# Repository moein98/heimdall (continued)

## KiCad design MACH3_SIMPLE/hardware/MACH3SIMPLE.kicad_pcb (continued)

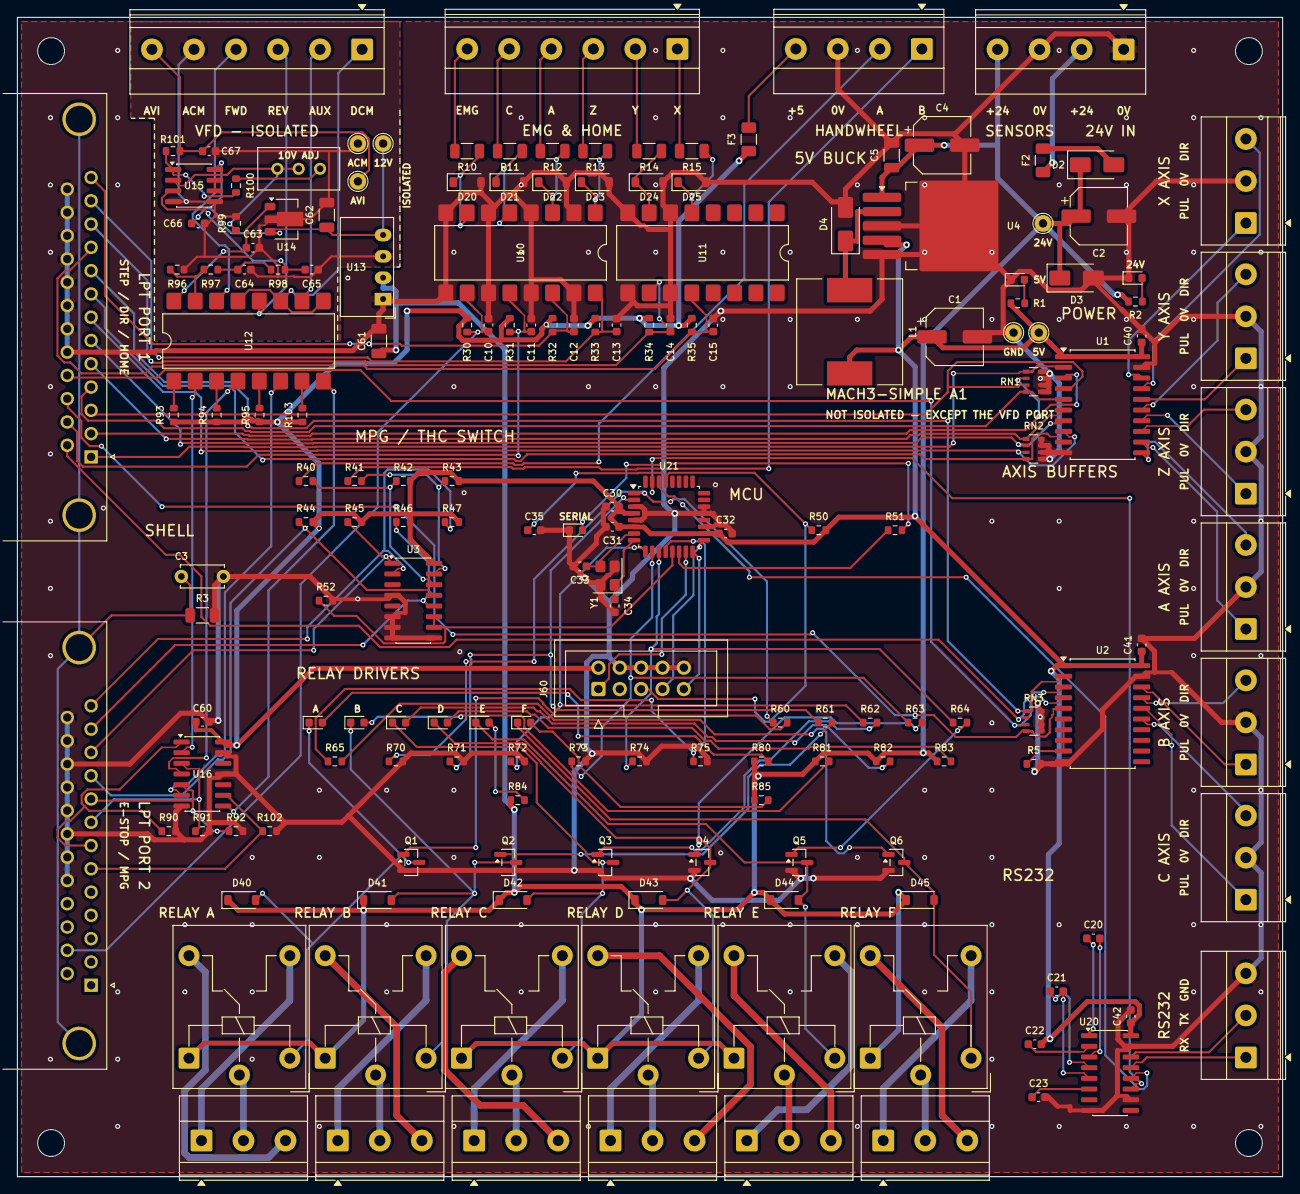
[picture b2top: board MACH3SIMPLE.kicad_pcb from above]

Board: 2 copper layers, 150.5 x 137.9 mm, 178 parts (0 on the bottom side), 149 nets.

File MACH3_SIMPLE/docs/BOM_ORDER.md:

# MACH3-SIMPLE - order list

Generated from the netlist by `tools/bom.py`. Quantities are what the
board needs; buy spares of the 0603 passives and the optocouplers.

## Semiconductors - the ones to get right

| Qty | Part | Package | Refs | Note |
|---:|---|---|---|---|
| 2 | 74HC245 | SOIC-20W_7.5x12.8mm_P1.27mm | U1, U2 |  |
| 2 | PC847 | SOIC-16 | U10, U11 | 4-channel opto, DIP-16 outline in SOIC. PC844 is the same part |
| 1 | 74HC4053 | SOIC-16 | U3 |  |
| 1 | ATmega328P-AU | TQFP-32 | U21 | TQFP-32. Runs on the 16 MHz crystal Y1 |
| 1 | MAX3232 | SOIC-16 | U20 | 3 V version works on 5 V; MAX232 does NOT - wrong capacitor values |

## Transistors, diodes and LEDs

| Qty | Part | Package | Refs | Note |
|---:|---|---|---|---|
| 9 | LED, indicator | 0603 SMD | D10, D11, D30, D50, D51, D52, D53, D54, D55 |  |
| 6 | 1N4148 | SOD-123 SMD | D40, D41, D42, D43, D44, D45 | plain small-signal, any maker |
| 6 | 2N7002 | SOT-23 | Q1, Q2, Q3, Q4, Q5, Q6 |  |
| 2 | SS34 | SMA SMD | D1, D2 | 40 V 3 A Schottky, both places |
| 1 | SMAJ26A | SMA SMD | D3 | TVS on the 24 V input. Clamps at 42 V, under the 50 V rating of C2 |

## Relays

| Qty | Part | Package | Refs | Note |
|---:|---|---|---|---|
| 6 | JQC-3FF-024-1Z | JQC-3FF relay, THT | K1, K2, K3, K4, K5, K6 | 24 V coil, SPDT. Songle or Hongfa |

## Connectors

| Qty | Part | Package | Refs | Note |
|---:|---|---|---|---|
| 13 | connector | Phoenix MKDS 1,5 5.0 mm, 3 way | J10, J11, J12, J13, J14, J15 ... J50 |  |
| 2 | connector | Phoenix MKDS 1,5 5.0 mm, 2 way | J3, J4 |  |
| 2 | connector | DB25 socket, right angle, PCB | J1, J2 |  |
| 1 | connector | Phoenix MKDS 1,5 5.0 mm, 6 way | J20 |  |
| 1 | connector | Phoenix MKDS 1,5 5.0 mm, 4 way | J30 |  |
| 1 | connector | 2x5 shrouded box header, 2.54 mm | J60 |  |

## Resistors

| Qty | Part | Package | Refs | Note |
|---:|---|---|---|---|
| 18 | 10k | 0603 SMD | R2, R30, R31, R32, R33, R34 ... R75 |  |
| 8 | 1k | 0603 SMD | R1, R51, R60, R61, R62, R63, R64, R65 |  |
| 8 | 4k7 | 0603 SMD | R42, R43, R80, R81, R82, R83, R84, R85 |  |
| 6 | 4k7 | 1206 SMD | R10, R11, R12, R13, R14, R15 |  |
| 3 | 4x10k | 4 x 0603 array, convex (1206 size) | RN1, RN2, RN3 |  |
| 2 | 330R | 0603 SMD | R40, R41 |  |
| 1 | 10k MPG_SEL | 0603 SMD | R52 |  |
| 1 | 10k spare | 0603 SMD | R5 |  |

## Capacitors

| Qty | Part | Package | Refs | Note |
|---:|---|---|---|---|
| 10 | 100nF | 0603 SMD | C20, C21, C22, C23, C30, C31, C32, C40, C41, C42 |  |
| 6 | 10nF | 0603 SMD | C10, C11, C12, C13, C14, C15 |  |
| 2 | 22pF | 0603 SMD | C33, C34 |  |
| 1 | 100uF 16V | electrolytic 6.3x7.7 SMD | C1 |  |
| 1 | 100uF 50V | electrolytic 6.3x7.7 SMD | C2 |  |
| 1 | 1nF 2kV | disc ceramic, THT | C3 |  |

## Inductor, fuse, crystal

| Qty | Part | Package | Refs | Note |
|---:|---|---|---|---|
| 2 | 1A slow | 1206 SMD | F1, F2 |  |
| 1 | 16MHz | 3.2x2.5 mm SMD, 4 pad | Y1 | load capacitance CL 18-20 pF, to suit the 22 pF capacitors |

## Mechanical

| Qty | Part | Package | Refs | Note |
|---:|---|---|---|---|
| 4 | M3 | M3 hole (no part) | H1, H2, H3, H4 |  |

## Not fitted - leave the pads empty

- R3 (0R link - DO NOT FIT)

**128 parts to fit** across 33 distinct lines.

Worth buying spare: the 0603 resistors and capacitors (they are pennies and
they get lost), one or two extra PC847, and one spare ATmega328P.

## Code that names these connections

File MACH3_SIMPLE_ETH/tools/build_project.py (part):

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# ---------------------------------------------------------------------------
# The RP2350B pin map. Keep in step with docs/SPEC.md and my_machine_map.h;
# tools/check_pinmap.py compares all three.
GPIO = {0: 'RS485_DI', 1: 'RS485_RO'}
for _i, _a in enumerate(AXES):
    GPIO[2 + _i] = '%s_STEP3' % _a           # PIO, consecutive
    GPIO[10 + _i] = '%s_DIR3' % _a           # consecutive
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                  footprint='Diode_SMD:D_SMA', rot=270)
    c24 = s.place('Device', 'C_Polarized', 'C104', '47uF 50V', 345.44, 88.9,
                  footprint='Capacitor_SMD:CP_Elec_6.3x7.7')
    s.net(j24, TOP_PIN(2, 4), 'VIN24')
    s.net(f24, 1, 'VIN24')
    s.link(f24, 2, d24, 2, 'VIN24F')
    s.link(d24, 1, tvs, 1, 'V24', via_y=76.2)
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    s.net(mcu, pins['ADC_AVDD'][0], '+3V3')
    s.net(mcu, pins['VREG_VIN'][0], '+3V3')
    s.net(mcu, pins['VREG_PGND'][0], 'GND')
    s.net(mcu, pins['VREG_LX'][0], 'VREG_LX')
    s.net(mcu, pins['VREG_FB'][0], '+1V1')
    s.net(mcu, pins['VREG_AVDD'][0], 'VREG_AVDD')
    s.net(mcu, pins['XIN'][0], 'XIN')
    s.net(mcu, pins['XOUT'][0], 'XOUT')
    s.net(mcu, pins['RUN'][0], 'NRST')
    s.net(mcu, pins['SWCLK'][0], 'SWCLK')
    s.net(mcu, pins['SWDIO'][0], 'SWDIO')
    s.net(mcu, pins['USB_DP'][0], 'USB_DP_MCU')
    s.net(mcu, pins['USB_DM'][0], 'USB_DM_MCU')
    for nm in ('QSPI_SD0', 'QSPI_SD1', 'QSPI_SD2', 'QSPI_SD3', 'QSPI_SCLK'):
        s.net(mcu, pins[nm][0], nm)
    s.net(mcu, pins['~{QSPI_SS}'][0], 'QSPI_SS')
    s.nc_rest(mcu)

    s.box(12.7, 35.56, 127.0, 157.48, 'CORE SUPPLY - INTERNAL SWITCHER')
    s.text('VREG_LX -> L201 -> +1V1 (DVDD). Tight loop to pins 62-65.', 15.24, 43.18)
    l = s.place('Device', 'L', 'L201', '3.3uH 2016 shielded', 50.8, 63.5,
                footprint='Inductor_SMD:L_Murata_DFE201610P', rot=90)
    s.net(l, 1, 'VREG_LX')
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
    rj = s.place('Connector', 'RJ45_Hanrun_HR911105A_Horizontal', 'J301', 'HR911105A',
                 495.3, 119.38, footprint='Connector_RJ:RJ45_Hanrun_HR911105A_Horizontal')
    for pin, net in (('1', 'ETH_TDP'), ('2', 'ETH_TDN'), ('4', 'ETH_TCT'),
                     ('3', 'ETH_RDP'), ('6', 'ETH_RDN'), ('5', 'ETH_RCT'),
                     ('8', 'CHASSIS'), ('SH', 'CHASSIS')):
        s.net(rj, pin, net)
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    s.net(tv, 3, 'GND')
    t = s.place('Connector', 'Conn_01x03_Pin', 'J801', 'RS485 A B GND', 223.52, 101.6,
                footprint=TERM % (3, 3))
    s.net(t, TOP_PIN(0, 3), 'RS485_A')
    s.net(t, TOP_PIN(1, 3), 'RS485_B')
    s.net(t, TOP_PIN(2, 3), 'GND')

    s.box(12.7, 165.1, 482.6, 381.0, 'HANDWHEEL MCU - ATmega328P, 3.3 V, 8 MHz, UART1 TO THE RP2350')
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    s.net(m, by['GND'], 'GND')
    s.net(m, by['AVCC'], '+3V3')
    s.nc(m, by['AREF'])
    s.net(m, by['~{RESET}/PC6'], 'HW_RESET')
    s.net(m, by['XTAL1/PB6'], 'HW_XTAL1')
    s.net(m, by['XTAL2/PB7'], 'HW_XTAL2')
    # RP2350 UART1 TX (GP42) -> ATmega RXD; ATmega TXD -> GP43.
    s.net(m, by['PD0'], 'UART1_TX')
    s.net(m, by['PD1'], 'UART1_RX')
    HW_PINS = (('PD2', 'MPG_A'), ('PD3', 'MPG_B'),          # INT0 / INT1
               ('PC0', 'MPG_SEL_X'), ('PC1', 'MPG_SEL_Y'), ('PC2', 'MPG_SEL_Z'),
               ('PC3', 'MPG_SEL_A'), ('PC4', 'MPG_SEL_B'), ('PC5', 'MPG_SEL_C'),
               ('PD4', 'MPG_SEL_U'), ('PD5', 'MPG_SEL_V'),
               ('PD6', 'MPG_X1'), ('PD7', 'MPG_X10'), ('PB0', 'MPG_X100'),
               ('PB1', 'HW_LED'),
               ('PB3', 'HW_MOSI'), ('PB4', 'HW_MISO'), ('PB5', 'HW_SCK'))
    for nm, net in HW_PINS:
        s.net(m, by[nm], net)
    s.nc_rest(m)
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    cap(s, 'C807', '22pF', 205.74, 368.3, 'HW_XTAL2', 'GND')
    isp = s.place('Connector', 'AVR-ISP-6', 'J802', 'HW ICSP', 205.74, 195.58,
                  footprint='Connector_PinHeader_2.54mm:PinHeader_2x03_P2.54mm_Vertical')
    for pin, net in (('1', 'HW_MISO'), ('2', '+3V3'), ('3', 'HW_SCK'), ('4', 'HW_MOSI'),
                     ('5', 'HW_RESET'), ('6', 'GND')):
        s.net(isp, pin, net)
    res(s, 'R805', '1k', 256.54, 220.98, 'HW_LED', 'HW_LED_A')
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
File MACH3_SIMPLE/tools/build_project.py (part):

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# nearest the top of the lower D-sub, the end closest to the spindle block.
# In Mach3: pin 7 is the spindle step/PWM pin, pin 8 Output #1 (M3, CW) and
# pin 9 Output #2 (M4, CCW).
P2_SPINDLE = [('7', 'SP_PWM_IN'), ('8', 'SP_FWD_IN'), ('9', 'SP_REV_IN'),
              ('6', 'SP_AUX_IN')]

# 24 V sensor channels, in the order they sit along the top edge.
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                  footprint='Capacitor_SMD:CP_Elec_6.3x7.7')
    # Labels, not a wire: pin 2 is drawn beside pin 1, and a wire from it to
    # the fuse would run across pin 1.
    s.net(j24, TOP_PIN(2, 4), 'VIN24')             # +24 in, third screw
    s.net(f24, 1, 'VIN24')
    s.link(f24, 2, d24, 2, 'VIN24F')
    s.link(d24, 1, tvs, 1, 'V24', via_y=76.2)
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    # The handwheel's +5V goes out on a cable, through a resettable fuse, so
    # a short in that cable trips F3 instead of pulling down the board's 5 V
    # rail and resetting the MCU with it.
    s.net(jm, TOP_PIN(0, 4), 'MPG_5V')
    pf = s.place('Device', 'Polyfuse', 'F3', '200mA hold PTC 1206', 190.5, 238.76,
                 footprint='Fuse:Fuse_1206_3216Metric')
    s.net(pf, 1, '+5V')
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    s.net(sw, '10', 'MPG_SEL')
    s.net(sw, '9', 'GND')            # C unused, its switch parked
    s.net(sw, '14', 'MPG_A_PC')      # X common: the conditioned A signal
    s.net(sw, '12', 'MPG_A_JOG')     # X0 -> port 2 pin 12
    s.net(sw, '13', 'MPG_A_THC')     # X1 -> port 2 pin 10
    s.net(sw, '15', 'MPG_B_PC')      # Y common
    s.net(sw, '2', 'MPG_B_JOG')      # Y0 -> port 2 pin 13
    s.net(sw, '1', 'MPG_B_THC')      # Y1 -> port 2 pin 11
    s.net(sw, '4', 'GND')            # Z switch unused
    s.nc(sw, '3')
    s.nc(sw, '5')
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    s.net(m, '8', 'GND')
    s.nc(m, '9')
    s.nc(m, '7')
    for pin, net in (('1', 'C1P'), ('3', 'C1N'), ('4', 'C2P'), ('5', 'C2N'),
                     ('2', 'VSP'), ('6', 'VSN')):
        s.net(m, pin, net)
    s.nc_rest(m)
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    c = s.place('Device', 'C', 'C42', '100nF', 63.5, 241.3, footprint=C0603)
    s.net(c, 1, '+5V')
    s.net(c, 2, 'GND')
    s.net(mcu, by['~{RESET}/PC6'] if '~{RESET}/PC6' in by else by.get('PC6', '29'),
          'MCU_RESET')
    rr = s.place('Device', 'R', 'R50', '10k', 25.4, 165.1, footprint=R0603)
    s.net(rr, 1, 'MCU_RESET')
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    cr = s.place('Device', 'C', 'C35', '10nF', 25.4, 190.5, footprint=C0603)
    s.net(cr, 1, 'MCU_RESET')
    s.net(cr, 2, 'GND')
    s.net(mcu, by['PD0'], 'MCU_RX')
    s.net(mcu, by['PD1'], 'MCU_TX')

    # A 16 MHz crystal. It was left off at first, by request, and put back
    # before the first order: the internal RC is trimmed only to within 10
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    xt = s.place('Device', 'Crystal_GND24', 'Y1', '16MHz',
                 101.6, 254.0,
                 footprint='Crystal:Crystal_SMD_3225-4Pin_3.2x2.5mm')
    s.net(mcu, by['XTAL1/PB6'], 'XTAL1')
    s.net(mcu, by['XTAL2/PB7'], 'XTAL2')
    s.net(xt, '3', 'XTAL1')
    s.net(xt, '1', 'XTAL2')
    s.net(xt, '2', 'GND')
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    # read back out of the netlist by firmware/test, which fails if the two
    # disagree.
    MCU_PINS = (
        ('PD3', 'REL_A'), ('PD4', 'REL_B'), ('PD5', 'REL_C'),
        ('PD6', 'REL_D'), ('PD7', 'REL_E'), ('PB0', 'REL_F'),
        ('PB1', 'MPG_SEL'),                   # SendSerial 'T' / 't'
        ('PB2', 'MCU_LED'),
        ('PB3', 'ICSP_MOSI'), ('PB4', 'ICSP_MISO'), ('PB5', 'ICSP_SCK'),
    )
    for nm, net in MCU_PINS:
        s.net(mcu, by[nm], net)
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
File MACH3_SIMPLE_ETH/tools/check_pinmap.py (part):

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difference.

It then follows each signal to where it must arrive (ETH_CS to the W5500's
SCS pin, UART1_TX to the handwheel MCU's RXD, each STEP line into a buffer
and out to its terminal, ...), and lists nets with a single node: a label
spelled differently at its two ends is a net of one on each side, which ERC
does not report.
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        expect(val('AUXINPUT%d_PIN' % n), net, 'AUXINPUT%d_PIN' % n)
    for n, net in enumerate(('RS485_DE', 'SP_PWM_IN', 'SP_FWD_IN', 'SP_REV_IN')):
        expect(val('AUXOUTPUT%d_PIN' % n), net, 'AUXOUTPUT%d_PIN' % n)
    for key, net in (('SPI_SCK_PIN', 'SPI_SCK'), ('SPI_MOSI_PIN', 'SPI_MOSI'),
                     ('SPI_MISO_PIN', 'SPI_MISO'), ('SD_CS_PIN', 'SD_CS'),
                     ('SPI_CS_PIN', 'ETH_CS'), ('SPI_IRQ_PIN', 'ETH_INT'),
                     ('I2C_SDA', 'I2C_SDA'), ('I2C_SCL', 'I2C_SCL'),
                     ('UART_TX_PIN', 'RS485_DI'), ('UART_RX_PIN', 'RS485_RO'),
                     ('UART_1_TX_PIN', 'UART1_TX'), ('UART_1_RX_PIN', 'UART1_RX')):
        expect(val(key), net, key)
    if defs.get('MODBUS_DIR_AUX') != '0':
        fails.append('MODBUS_DIR_AUX should be aux output 0 (GP25)')
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              ('SPI_MISO', 'J203', 'DAT0'), ('SPI_SCK', 'J203', 'CLK'),
              ('RS485_DI', 'U801', 'DI'), ('RS485_RO', 'U801', 'RO'),
              ('RS485_DE', 'U801', 'DE'), ('RS485_DE', 'U801', '~{RE}'),
              ('UART1_TX', 'U802', 'PD0'), ('UART1_RX', 'U802', 'PD1'),
              ('I2C_SDA', 'U601', 'SDA'), ('I2C_SCL', 'U601', 'SCK'),
              ('SP_PWM_IN', 'U701', '1'), ('SP_FWD_IN', 'U701', '3'),
              ('SP_REV_IN', 'U701', '5'), ('SP_AUX_IN', 'U701', '9'),
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
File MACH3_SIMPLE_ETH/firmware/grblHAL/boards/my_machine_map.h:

/*
  my_machine_map.h - MACH3-SIMPLE-ETH, RP2350B (80-pin, GPIO0-47), W5500 Ethernet

  Eight independent axes (X Y Z A B C U V), every GPIO used:

    GP0  GP1        UART0 TX/RX   -> RS485 transceiver, Modbus VFD   (stream 0)
    GP2  .. GP9     STEP X Y Z A B C U V (PIO, must be consecutive)
    GP10 .. GP17    DIR  X Y Z A B C U V (consecutive, GPIO_SHIFT10)
    GP18            stepper enable, all axes
    GP19            SD card CS
    GP20 .. GP23    SPI0 MISO, W5500 CS, SCK, MOSI (W5500 and SD share SPI0)
    GP24            W5500 INT
    GP25            RS485 DE/RE (Modbus direction, aux out 0)
    GP26 .. GP33    LIMIT X Y Z A B C U V
    GP34 .. GP37    E-STOP, FEED HOLD, CYCLE START, PROBE
    GP38 .. GP40    ARC OK, THC UP, THC DOWN (plasma plugin, aux in)
    GP41            spindle PWM (-> isolated 0-10 V)
    GP42 GP43       UART1 TX/RX   -> handwheel MCU, MPG mode 2       (stream 1)
    GP44 GP45       spindle enable (FWD), direction (REV)
    GP46 GP47       I2C1 SDA/SCL  -> MCP23017: port A = 6 relays + spindle AUX + LED,
                                                port B = 8 spare inputs

  W5500 reset is tied to the board reset, so it needs no GPIO.
  UART, SPI and I2C pins checked against the SDK FUNCSEL table (io_bank0.h):
  UART0 0/1, UART1 42/43 (UART_AUX on RP2350), SPI0 20-23, I2C1 46/47.

  Part of grblHAL, GPLv3 - see COPYING.
*/

#if TRINAMIC_ENABLE
#error Trinamic plugin not supported!
#endif

#if N_ABC_MOTORS > 5
#error "Axis configuration is not supported!"
#endif

#if RP_MCU != 2350
#error "Board has a RP2350B processor! Build with PICO_BOARD=pimoroni_pga2350 or a RP2350B board file."
#endif

#define BOARD_NAME "MACH3-SIMPLE-ETH"

#undef I2C_ENABLE
#define I2C_ENABLE              1

// Step pulses: PIO, eight consecutive pins from STEP_PINS_BASE.
#define STEP_PORT               GPIO_PIO
#define STEP_PINS_BASE          2

// Direction: eight consecutive pins from X_DIRECTION_PIN.
#define DIRECTION_PORT          GPIO_OUTPUT
#define X_DIRECTION_PIN         10
#define Y_DIRECTION_PIN         11
#define Z_DIRECTION_PIN         12
#define DIRECTION_OUTMODE       GPIO_SHIFT10

#define ENABLE_PORT             GPIO_OUTPUT
#define STEPPERS_ENABLE_PIN     18

#define X_LIMIT_PIN             26
#define Y_LIMIT_PIN             27
#define Z_LIMIT_PIN             28
#define LIMIT_INMODE            GPIO_MAP

#if N_ABC_MOTORS > 0
#define M3_AVAILABLE
#define M3_STEP_PIN             (STEP_PINS_BASE + 3)
#define M3_DIRECTION_PIN        (X_DIRECTION_PIN + 3)
#define M3_LIMIT_PIN            29
#endif
#if N_ABC_MOTORS > 1
#define M4_AVAILABLE
#define M4_STEP_PIN             (STEP_PINS_BASE + 4)
#define M4_DIRECTION_PIN        (X_DIRECTION_PIN + 4)
#define M4_LIMIT_PIN            30
#endif
#if N_ABC_MOTORS > 2
#define M5_AVAILABLE
#define M5_STEP_PIN             (STEP_PINS_BASE + 5)
#define M5_DIRECTION_PIN        (X_DIRECTION_PIN + 5)
#define M5_LIMIT_PIN            31
#endif
#if N_ABC_MOTORS > 3
#define M6_AVAILABLE
#define M6_STEP_PIN             (STEP_PINS_BASE + 6)
#define M6_DIRECTION_PIN        (X_DIRECTION_PIN + 6)
#define M6_LIMIT_PIN            32
#endif
#if N_ABC_MOTORS > 4
#define M7_AVAILABLE
#define M7_STEP_PIN             (STEP_PINS_BASE + 7)
#define M7_DIRECTION_PIN        (X_DIRECTION_PIN + 7)
#define M7_LIMIT_PIN            33
#endif

// Auxiliary outputs.
#define AUXOUTPUT0_PORT         GPIO_OUTPUT // RS485 DE/RE
#define AUXOUTPUT0_PIN          25
#define AUXOUTPUT1_PORT         GPIO_OUTPUT // Spindle PWM
#define AUXOUTPUT1_PIN          41
#define AUXOUTPUT2_PORT         GPIO_OUTPUT // Spindle enable (VFD FWD)
#define AUXOUTPUT2_PIN          44
#define AUXOUTPUT3_PORT         GPIO_OUTPUT // Spindle direction (VFD REV)
#define AUXOUTPUT3_PIN          45

#if DRIVER_SPINDLE_ENABLE
#define SPINDLE_PORT            GPIO_OUTPUT
#endif
#if DRIVER_SPINDLE_ENABLE & SPINDLE_PWM
#define SPINDLE_PWM_PIN         AUXOUTPUT1_PIN
#endif
#if DRIVER_SPINDLE_ENABLE & SPINDLE_ENA
#define SPINDLE_ENABLE_PIN      AUXOUTPUT2_PIN
#endif
#if DRIVER_SPINDLE_ENABLE & SPINDLE_DIR
#define SPINDLE_DIRECTION_PIN   AUXOUTPUT3_PIN
#endif

// Auxiliary inputs.
#define AUXINPUT0_PIN           34 // E-stop
#define AUXINPUT1_PIN           35 // Feed hold
#define AUXINPUT2_PIN           36 // Cycle start
#define AUXINPUT3_PIN           37 // Probe
#define AUXINPUT4_PIN           38 // Arc OK
#define AUXINPUT5_PIN           39 // THC up
#define AUXINPUT6_PIN           40 // THC down

#if CONTROL_ENABLE & CONTROL_HALT
#define RESET_PIN               AUXINPUT0_PIN
#endif
#if CONTROL_ENABLE & CONTROL_FEED_HOLD
#define FEED_HOLD_PIN           AUXINPUT1_PIN
#endif
#if CONTROL_ENABLE & CONTROL_CYCLE_START
#define CYCLE_START_PIN         AUXINPUT2_PIN
#endif
#if PROBE_ENABLE
#define PROBE_PIN               AUXINPUT3_PIN
#endif

// SPI0: W5500 and SD card.
#if SDCARD_ENABLE || ETHERNET_ENABLE
#define SPI_PORT                0
#define SPI_SCK_PIN             22
#define SPI_MOSI_PIN            23
#define SPI_MISO_PIN            20
#if SDCARD_ENABLE
#define SD_CS_PIN               19
#endif
#if ETHERNET_ENABLE
#define SPI_CS_PIN              21
#define SPI_IRQ_PIN             24
#define WIZNET_CS_PIN           SPI_CS_PIN
#endif
#endif

// I2C1: MCP23017 (relays), optional FRAM.
#if I2C_ENABLE
#define I2C_PORT                1
#define I2C_SDA                 46
#define I2C_SCL                 47
#endif

// UART0: RS485 / Modbus VFD. UART1: handwheel MCU (MPG).
#define UART_TX_PIN             0
#define UART_RX_PIN             1
#define SERIAL1_PORT            1
#define UART_1_TX_PIN           42
#define UART_1_RX_PIN           43

#if MODBUS_ENABLE
#define MODBUS_RTU_STREAM       0
#undef MODBUS_ENABLE
#define MODBUS_ENABLE           (MODBUS_RTU_ENABLED|MODBUS_RTU_DIR_ENABLED)
#define MODBUS_DIR_AUX          0
#endif

// MPG_STREAM defaults to 1 (UART1) when Modbus has stream 0.
